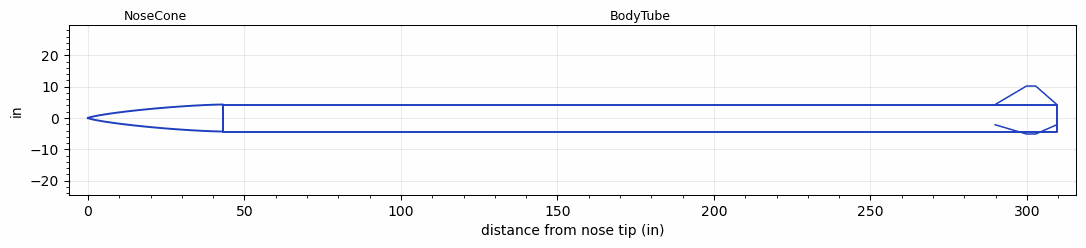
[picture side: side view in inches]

<RASAeroDocument>
 <FileVersion>2</FileVersion>
 <RocketDesign>
  <NoseCone>
   <Length>43.125</Length>
   <Diameter>8.625</Diameter>
   <Shape>Von Karman Ogive</Shape>
   <Location>0</Location>
  </NoseCone>
  <BodyTube>
   <Length>266.436</Length>
   <Diameter>8.625</Diameter>
   <Location>43.125</Location>
   <Fin>
    <Count>3</Count>
    <Chord>19.685</Chord>
    <Span>5.9055</Span>
    <SweepDistance>10</SweepDistance>
    <TipChord>2.9527</TipChord>
    <Thickness>0.16</Thickness>
    <Location>19.685</Location>
    <AirfoilSection>Hexagonal</AirfoilSection>
    <FX1>0.5</FX1>
    <FX3>0.5</FX3>
   </Fin>
  </BodyTube>
  <Surface>Sheet Metal</Surface>
  <ModifiedBarrowman>False</ModifiedBarrowman>
  <Turbulence>False</Turbulence>
  <UseBooster1>False</UseBooster1>
  <UseBooster2>False</UseBooster2>
 </RocketDesign>
 <LaunchSite>
  <Altitude>4000</Altitude>
  <Pressure>29.43</Pressure>
  <RodAngle>0</RodAngle>
  <RodLength>43</RodLength>
  <Temperature>95</Temperature>
  <WindSpeed>5</WindSpeed>
 </LaunchSite>
 <Recovery>
  <Altitude1>1000</Altitude1>
  <Altitude2>1000</Altitude2>
  <DeviceType1>None</DeviceType1>
  <DeviceType2>None</DeviceType2>
  <Event1>False</Event1>
  <Event2>False</Event2>
  <Size1>1</Size1>
  <Size2>1</Size2>
  <EventType1>None</EventType1>
  <EventType2>None</EventType2>
  <CD1>1.33</CD1>
  <CD2>1.33</CD2>
 </Recovery>
</RASAeroDocument>
